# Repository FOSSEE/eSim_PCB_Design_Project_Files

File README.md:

## Task 7 – ESP32-S3 PCB Design Submission

Dear FOSSEE eSim Team,

I am submitting my PCB design as part of the eSim Semester Long Internship – Autumn 2026, Screening Task 7.

### Project Title
ESP32-S3 Development and Interface PCB

### Project Description
The project involves designing a custom PCB integrating an ESP32-S3-WROOM-1 module, 3.3 V voltage regulation, external interfacing connectors and status indication circuitry.

### Submitted Files
- KiCad schematic and PCB project files
- PCB design proposal
- Technical design documentation
- PCB layout and 3D-view images
- Manufacturing files, where applicable

The repository contains the project files and supporting documentation for review.

Thank you for your consideration.

**Submitted by:**  
Siddhant Monde  
Electronics and Telecommunication Engineering  
St. Francis Institute of Technology, Mumbai

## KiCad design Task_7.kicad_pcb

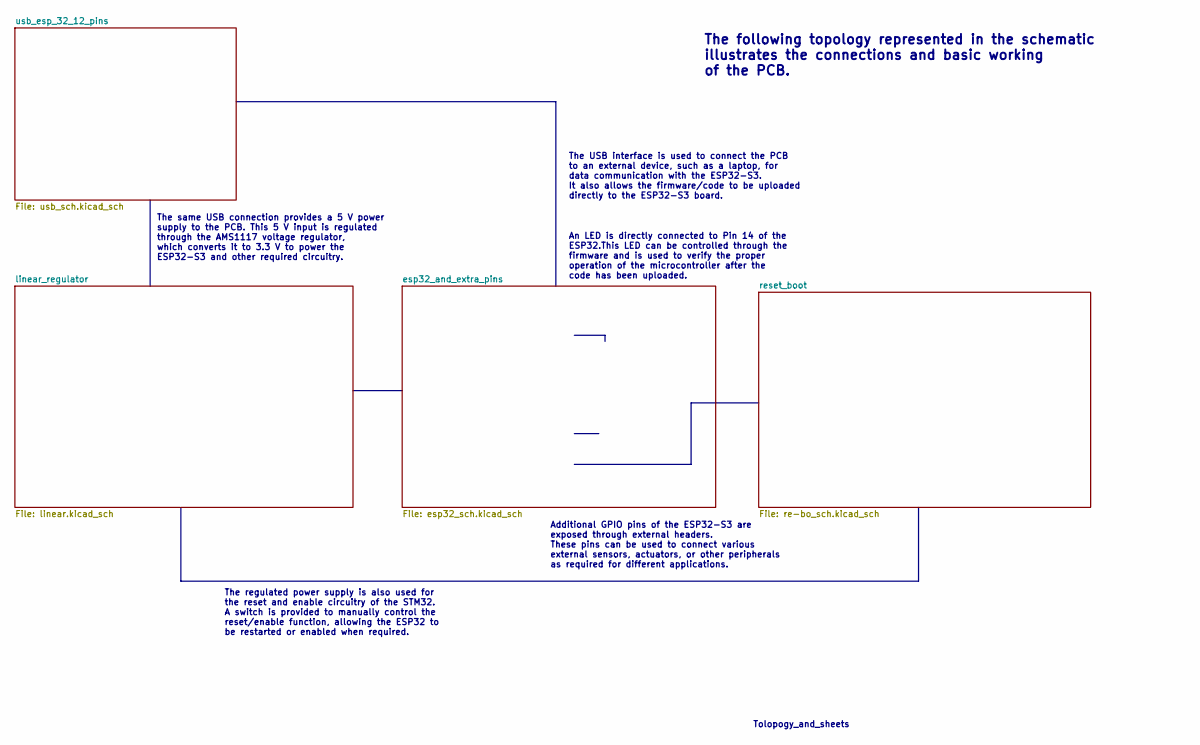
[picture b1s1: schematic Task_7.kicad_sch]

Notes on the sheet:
The following topology represented in the schematic illustrates the connections and basic working of the PCB.
The regulated power supply is also used for the reset and enable circuitry of the STM32. A switch is provided to manually control the reset/enable function, allowing the ESP32 to be restarted or enabled when required.
Additional GPIO pins of the ESP32-S3 are exposed through external headers. These pins can be used to connect various external sensors, actuators, or other peripherals as required for different applications.
The same USB connection provides a 5 V power supply to the PCB. This 5 V input is regulated through the AMS1117 voltage regulator, which converts it to 3.3 V to power the ESP32-S3 and other required circuitry.
The USB interface is used to connect the PCB to an external device, such as a laptop, for data communication with the ESP32-S3. It also allows the firmware/code to be uploaded directly to the ESP32-S3 board.
Tolopogy_and_sheets
An LED is directly connected to Pin 14 of the ESP32.This LED can be controlled through the firmware and is used to verify the proper operation of the microcontroller after the code has been uploaded.

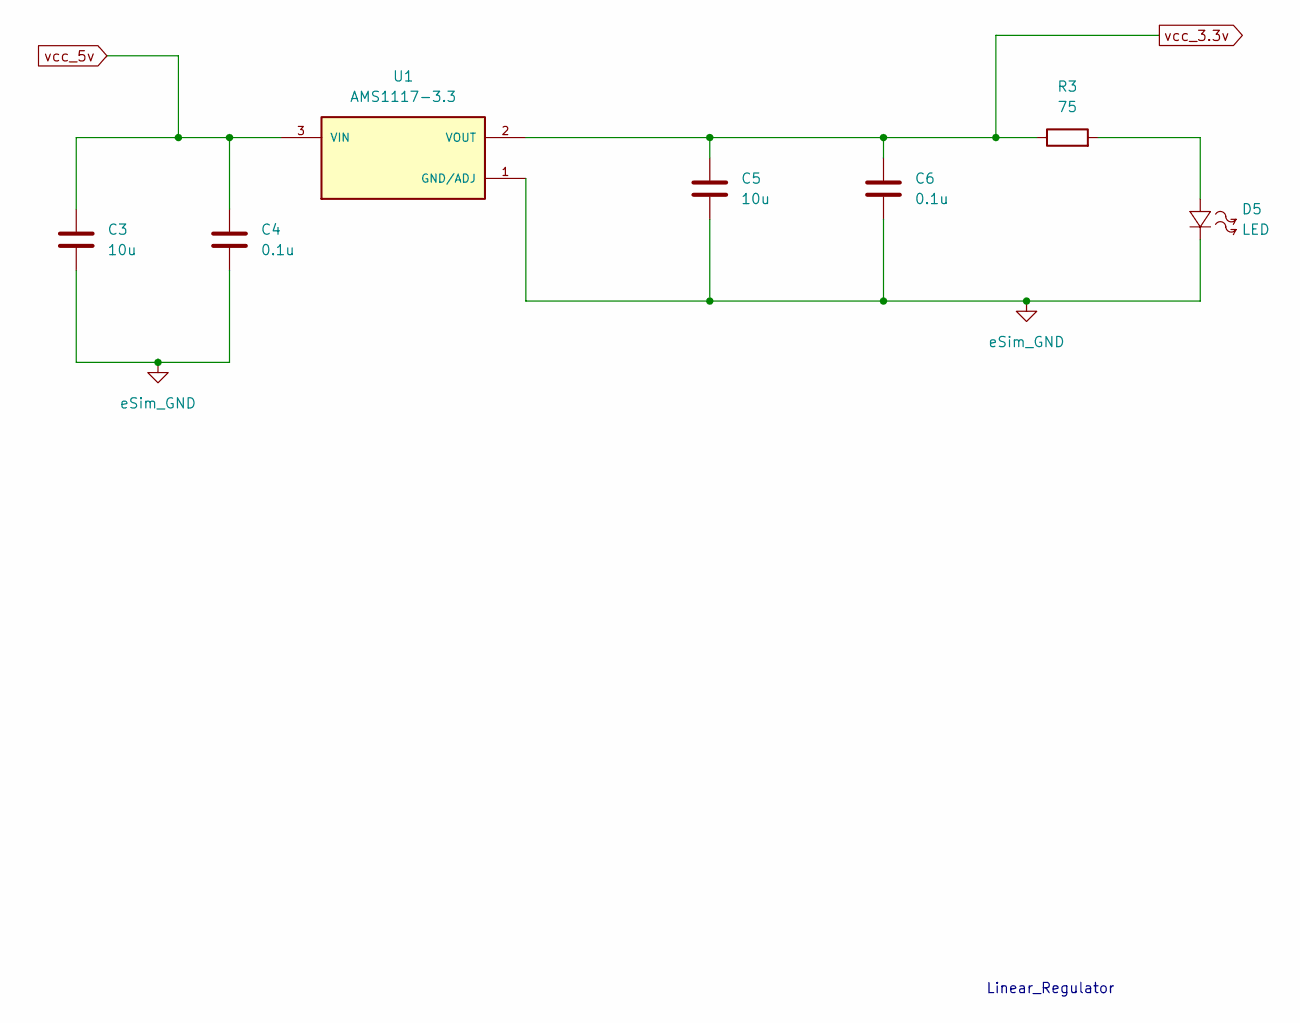
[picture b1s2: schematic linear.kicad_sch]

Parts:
C3, C5: 10u; CP_EIA-1608-08_AVX-J
C4, C6: 0.1u; CP_EIA-1608-08_AVX-J
D5: LED; LED_0805_2012Metric
R3: 75; R_0603_1608Metric
U1: AMS1117-3.3; ams117_footprint; PARTREV N/A

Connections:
GND: C3.1, C4.1, C5.1, C6.1, D5.2 (-), U1.1 (GND/ADJ); also elsewhere on the board
unnamed: D5.1 (+), R3.2
vcc_3.3v: C5.2, C6.2, R3.1, U1.2 (VOUT); also elsewhere on the board
vcc_5v: C3.2, C4.2, U1.3 (VIN); also elsewhere on the board

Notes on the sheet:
Linear_Regulator

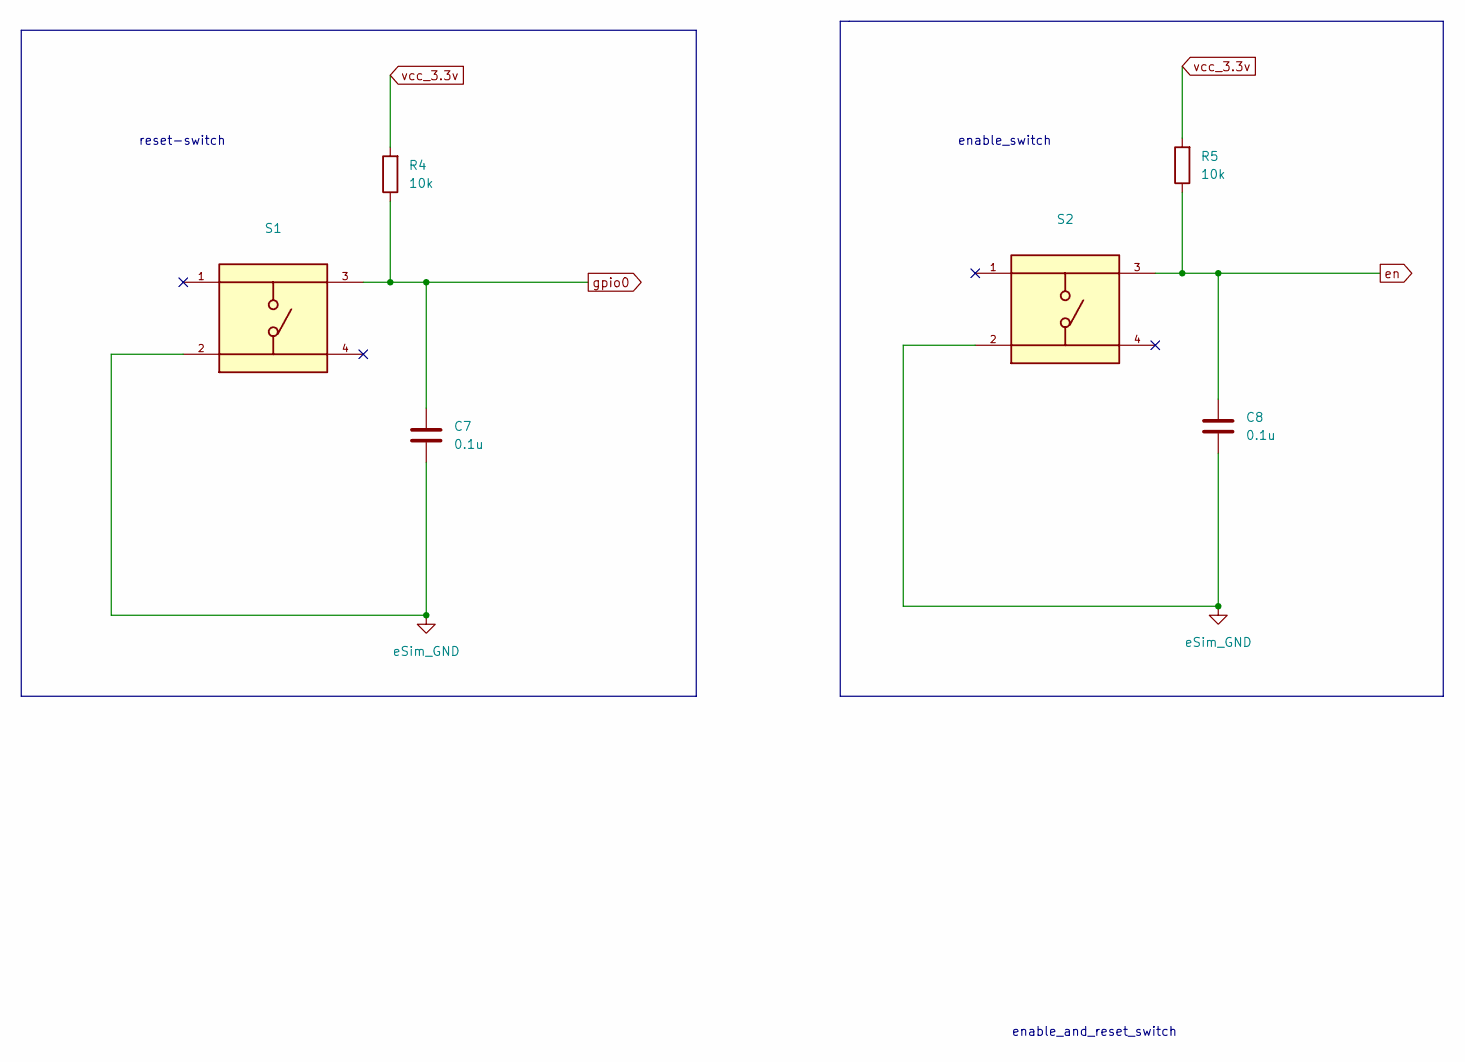
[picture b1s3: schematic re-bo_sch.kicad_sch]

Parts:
C7, C8: 0.1u; CP_EIA-1608-08_AVX-J
R4, R5: 10k; R_0603_1608Metric
S1, S2: TS04-66-55-BK-100-SMT; SW_Push_2P1T_Toggle_CK_PVA1xxH3xxxxxxV2; PARTREV 1.0

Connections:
GND: C7.2, C8.2, S1.2, S2.2; also elsewhere on the board
en: C8.1, R5.1, S2.3; also elsewhere on the board
gpio0: C7.1, R4.1, S1.3; also elsewhere on the board
vcc_3.3v: R4.2, R5.2; also elsewhere on the board

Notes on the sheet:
enable_switch
reset-switch
enable_and_reset_switch

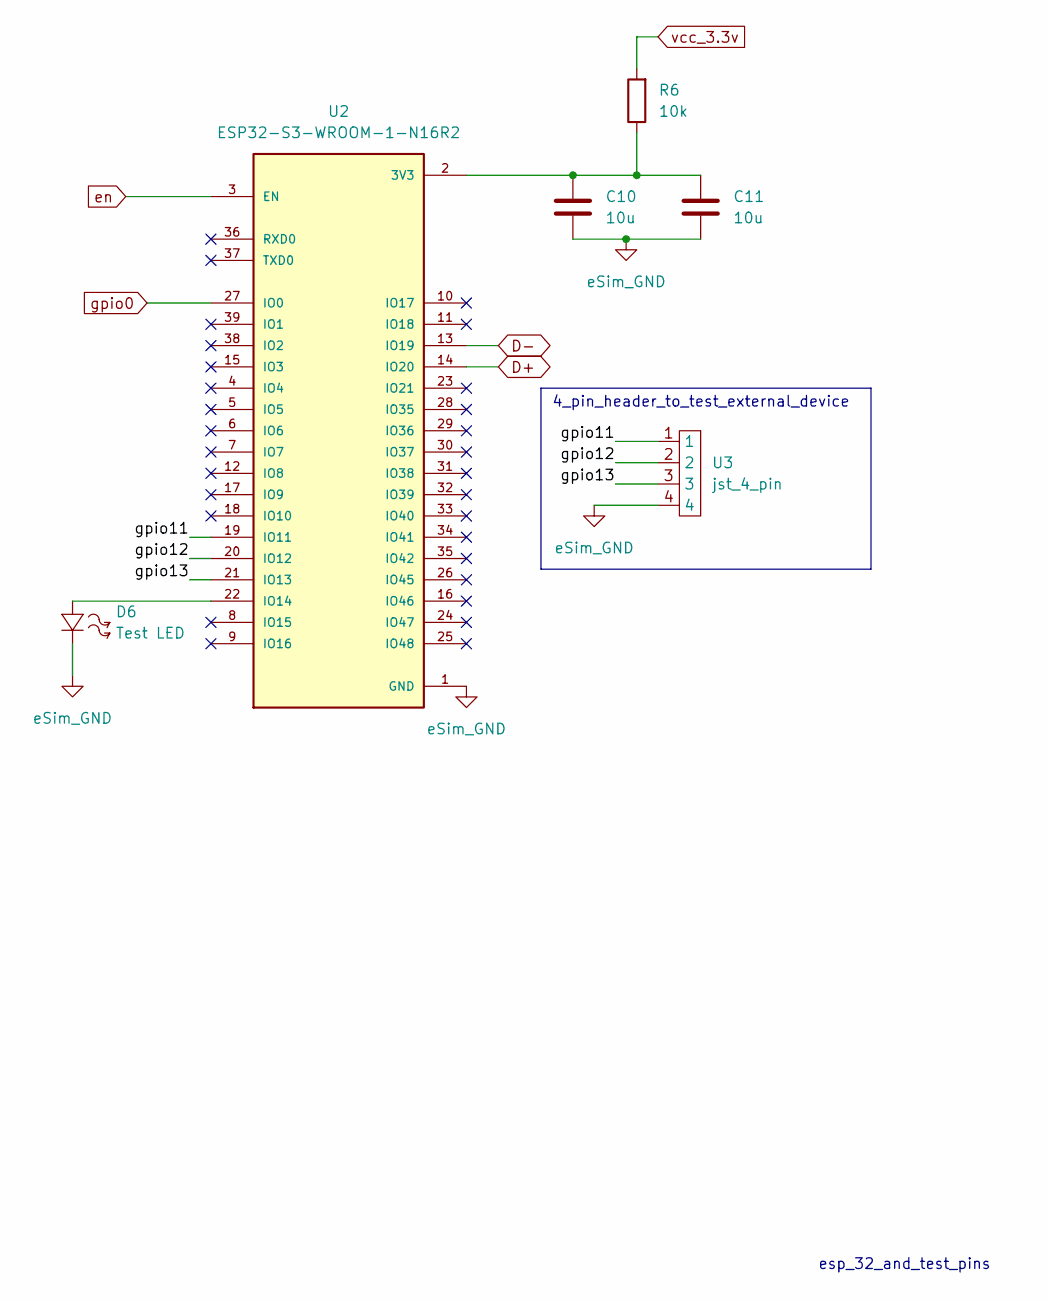
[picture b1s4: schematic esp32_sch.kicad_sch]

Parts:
C10, C11: 10u; CP_EIA-1608-08_AVX-J
D6: Test LED; LED_0805_2012Metric
R6: 10k; R_0603_1608Metric
U2: ESP32-S3-WROOM-1-N16R2; XCVR_ESP32-S3-WROOM-1-N16R2; PARTREV v1.0
U3: jst_4_pin; JST_EH_B4B-EH-A_1x04_P2.50mm_Vertical

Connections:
/esp32_and_extra_pins/gpio11: U2.19 (IO11), U3.1
/esp32_and_extra_pins/gpio12: U2.20 (IO12), U3.2
/esp32_and_extra_pins/gpio13: U2.21 (IO13), U3.3
D+: U2.14 (IO20); also elsewhere on the board
D-: U2.13 (IO19); also elsewhere on the board
GND: C10.2, C11.2, D6.2 (-), U2.1 (GND), U2.40 (GND), U2.41_1 (GND), U2.41_2 (GND), U2.41_3 (GND), U2.41_4 (GND), U2.41_5 (GND), U2.41_6 (GND), U2.41_7 (GND), U2.41_8 (GND), U2.41_9 (GND), U2.41_14, U3.4; also elsewhere on the board
unnamed: C10.1, C11.1, R6.1, U2.2 (3V3)
unnamed: D6.1 (+), U2.22 (IO14)
en: U2.3 (EN); also elsewhere on the board
gpio0: U2.27 (IO0); also elsewhere on the board
vcc_3.3v: R6.2; also elsewhere on the board

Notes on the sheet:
4_pin_header_to_test_external_device
esp_32_and_test_pins

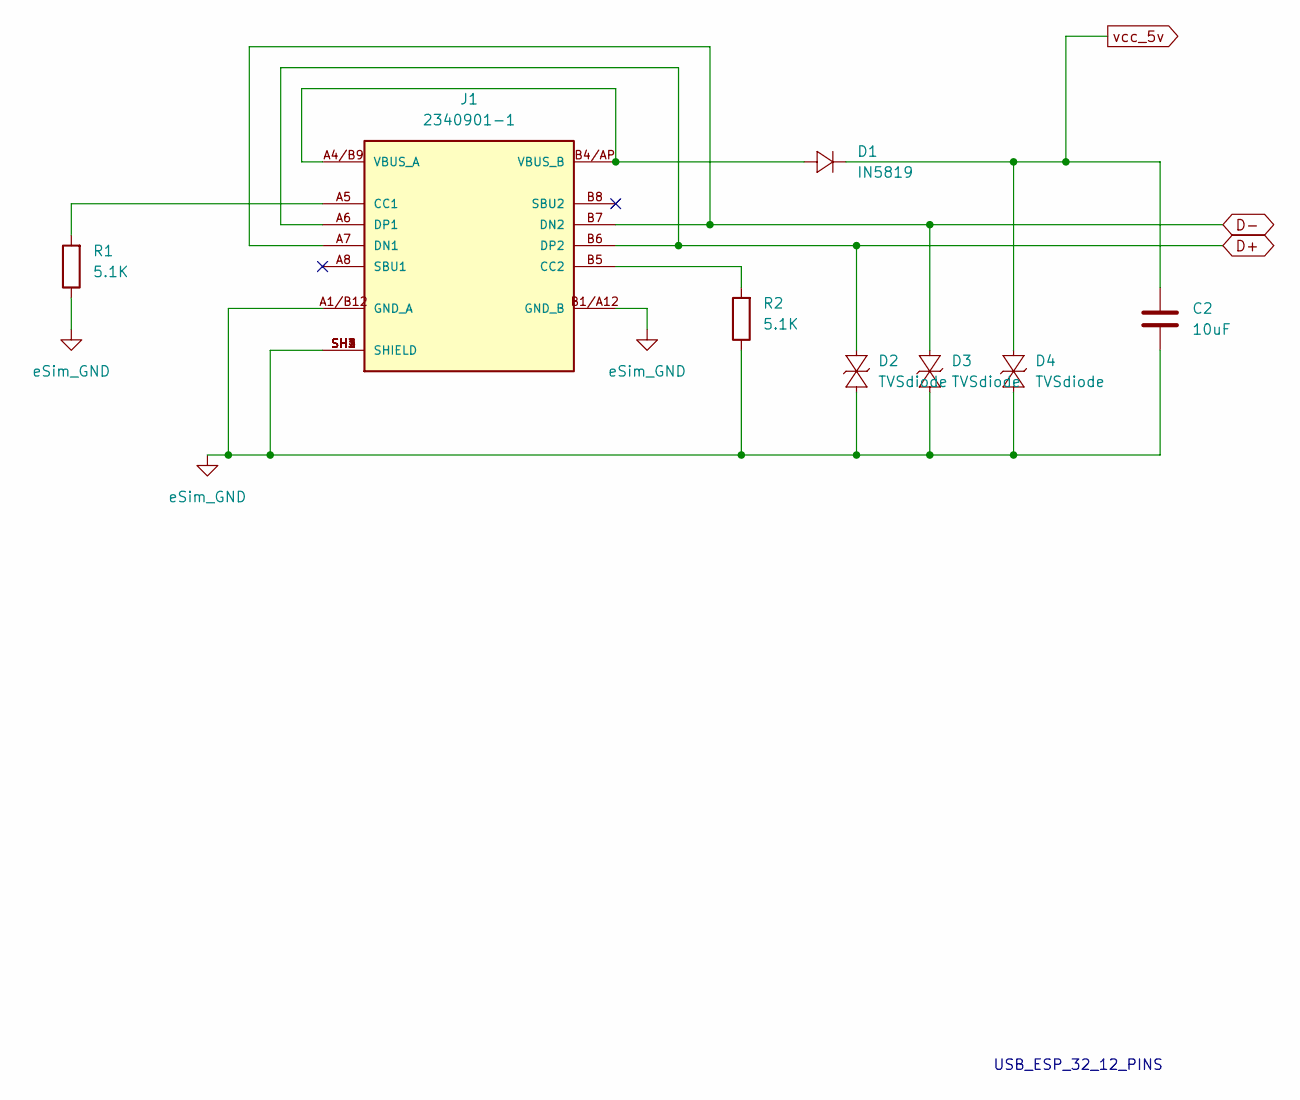
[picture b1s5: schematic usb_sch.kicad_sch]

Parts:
C2: 10uF; CP_EIA-1608-08_AVX-J
D1: IN5819; D_0603_1608Metric
D2, D3, D4: TVSdiode; D_0603_1608Metric
J1: 2340901-1; TE_2340901-1; PARTREV A
R1, R2: 5.1K; R_0603_1608Metric

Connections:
D+: D2.1 (+), J1.A6 (DP1), J1.B6 (DP2); also elsewhere on the board
D-: D3.1 (+), J1.A7 (DN1), J1.B7 (DN2); also elsewhere on the board
GND: C2.2, D2.2 (-), D3.2 (-), D4.2 (-), J1.A1/B12 (GND_A), J1.B1/A12 (GND_B), J1.SH1 (SHIELD), J1.SH2 (SHIELD), J1.SH3 (SHIELD), J1.SH4 (SHIELD), R1.1, R2.1; also elsewhere on the board
unnamed: D1.1 (+), J1.A4/B9 (VBUS_A), J1.B4/AP (VBUS_B)
unnamed: J1.A5 (CC1), R1.2
unnamed: J1.B5 (CC2), R2.2
vcc_5v: C2.1, D1.2 (-), D4.1 (+); also elsewhere on the board

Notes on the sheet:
USB_ESP_32_12_PINS

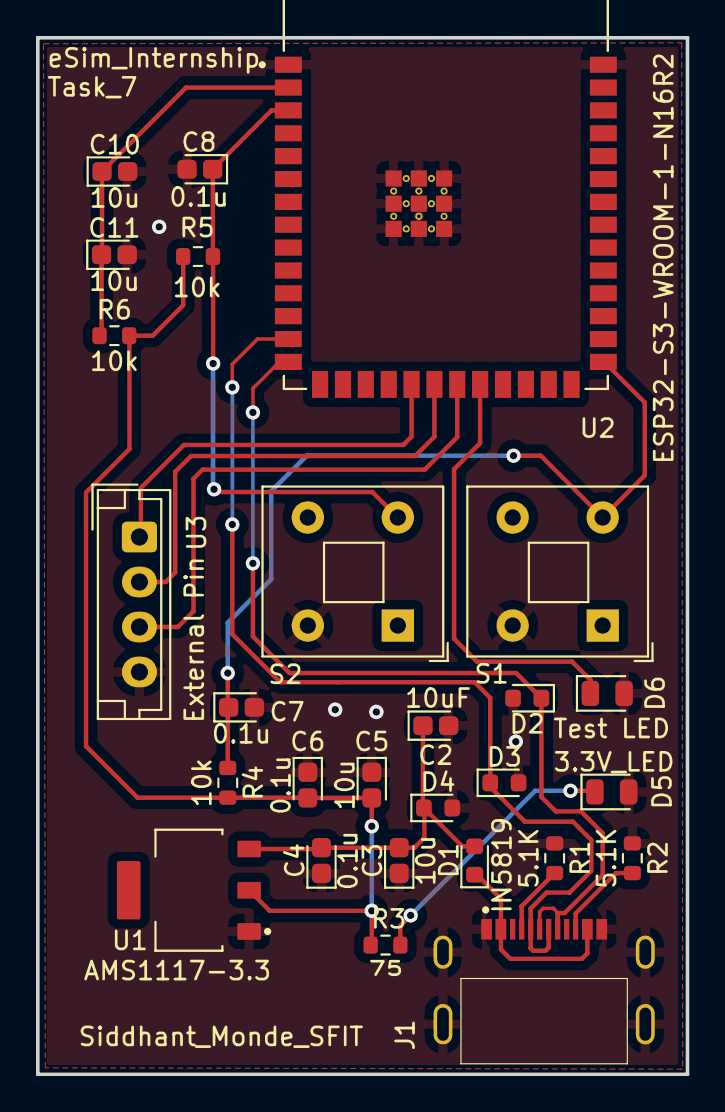
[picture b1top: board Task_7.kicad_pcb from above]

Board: 2 copper layers, 36.1 x 57.6 mm, 27 parts (0 on the bottom side), 16 nets.

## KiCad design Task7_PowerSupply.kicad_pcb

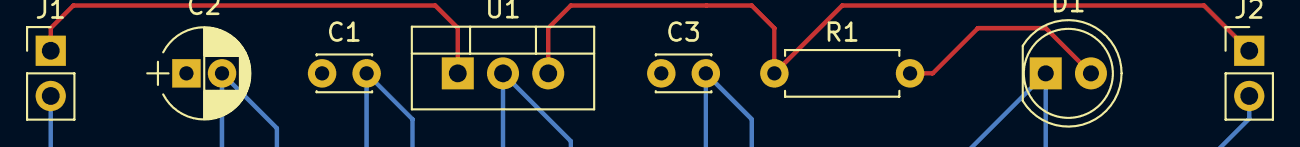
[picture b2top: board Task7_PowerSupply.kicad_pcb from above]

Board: 2 copper layers, 8 parts (0 on the bottom side), 4 nets.

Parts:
C1, C3: eSim_C; C_Disc_D3.0mm_W2.0mm_P2.50mm
C2: eSim_CP1; CP_Radial_D5.0mm_P2.00mm
D1: eSim_LED; LED_D5.0mm
J1, J2: Conn_01x02; Pin_Header_Straight_1x02_Pitch2.54mm
R1: eSim_R; R_Axial_DIN0207_L6.3mm_D2.5mm_P7.62mm_Horizontal
U1: L7805; TO-220_Vertical

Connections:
unnamed: C1.2, C2.2, C3.2, D1.1, J1.2, J2.2, U1.2
unnamed: D1.2, R1.2
unnamed: J1.1, U1.1
unnamed: J2.1, R1.1, U1.3

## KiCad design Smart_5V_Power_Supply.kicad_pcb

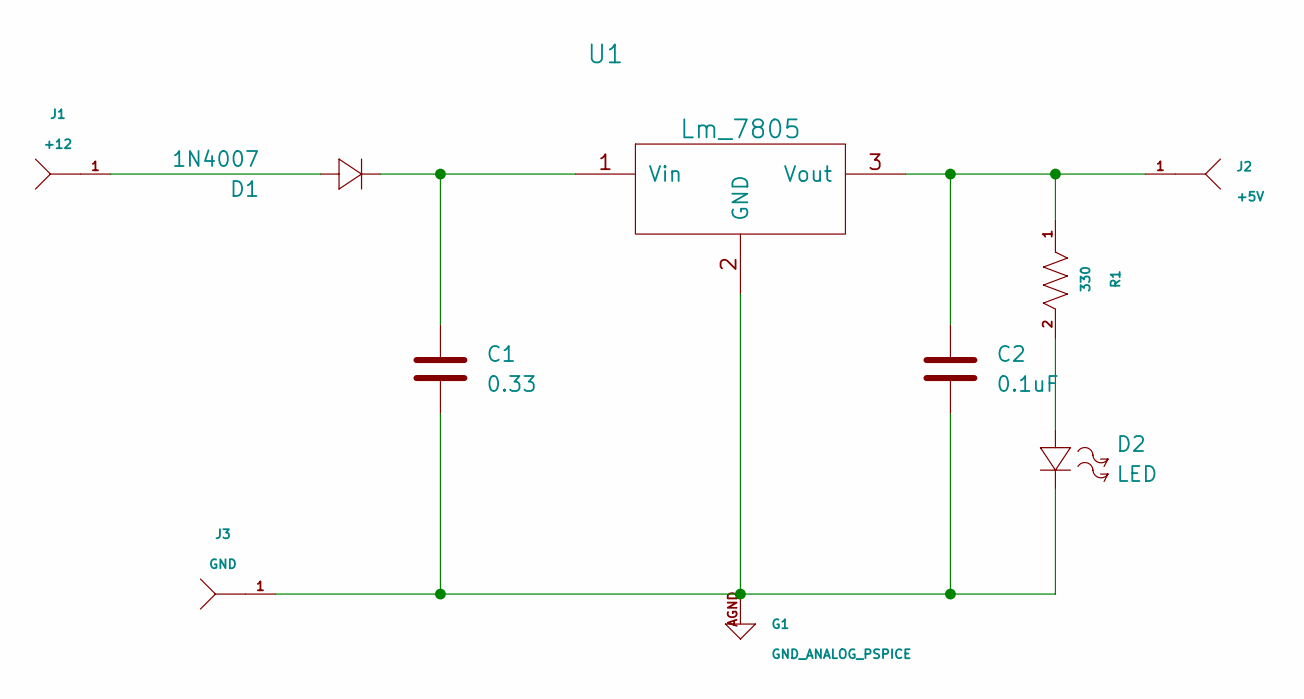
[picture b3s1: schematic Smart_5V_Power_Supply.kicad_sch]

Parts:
C1: 0.33; C_Disc_D5.1mm_W3.2mm_P5.00mm
C2: 0.1uF; C_Disc_D5.1mm_W3.2mm_P5.00mm
D1: 1N4007; D_DO-41_SOD81_P10.16mm_Horizontal
D2: LED; LED_D5.0mm
G1: GND_ANALOG_PSPICE
J1: +12; PinHeader_1x01_P2.54mm_Vertical
J2: +5V; PinHeader_1x01_P2.54mm_Vertical
J3: GND; PinHeader_1x01_P2.54mm_Vertical
R1: 330; R_Axial_DIN0207_L6.3mm_D2.5mm_P10.16mm_Horizontal
U1: Lm_7805; TO-220-3_Vertical

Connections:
unnamed: C1.1, D1.2 (-), U1.1 (Vin)
unnamed: C1.2, C2.2, D2.2 (-), G1.AGND, J3.1, U1.2 (GND)
unnamed: C2.1, J2.1, R1.1, U1.3 (Vout)
unnamed: D1.1 (+), J1.1
unnamed: D2.1 (+), R1.2

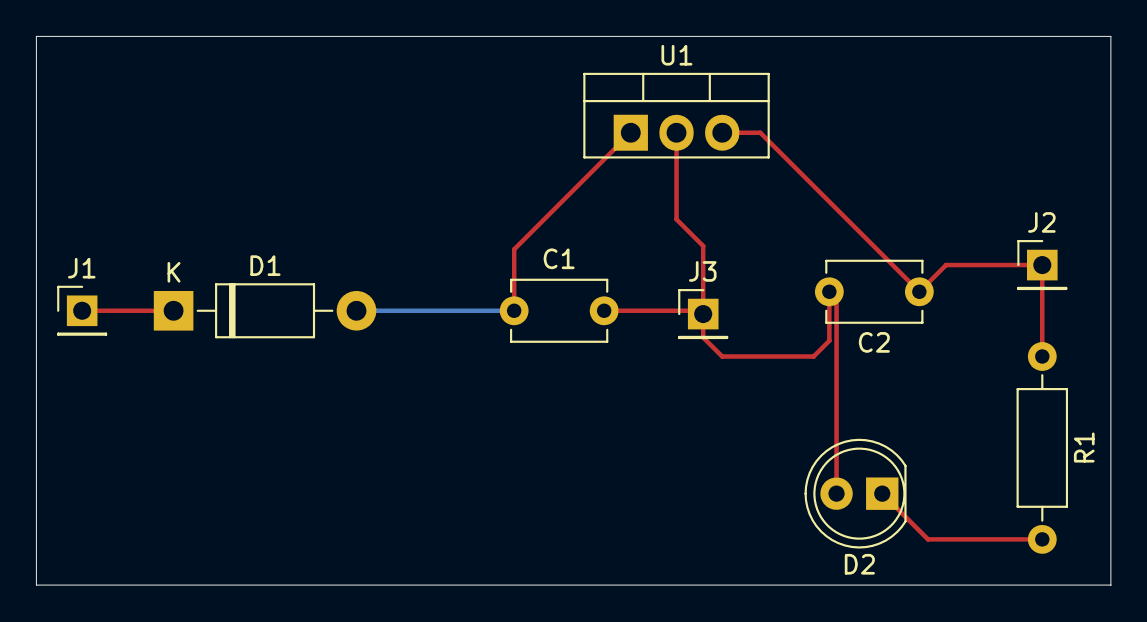
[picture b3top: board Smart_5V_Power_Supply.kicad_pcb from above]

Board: 2 copper layers, 59.7 x 30.5 mm, 9 parts (0 on the bottom side), 5 nets.

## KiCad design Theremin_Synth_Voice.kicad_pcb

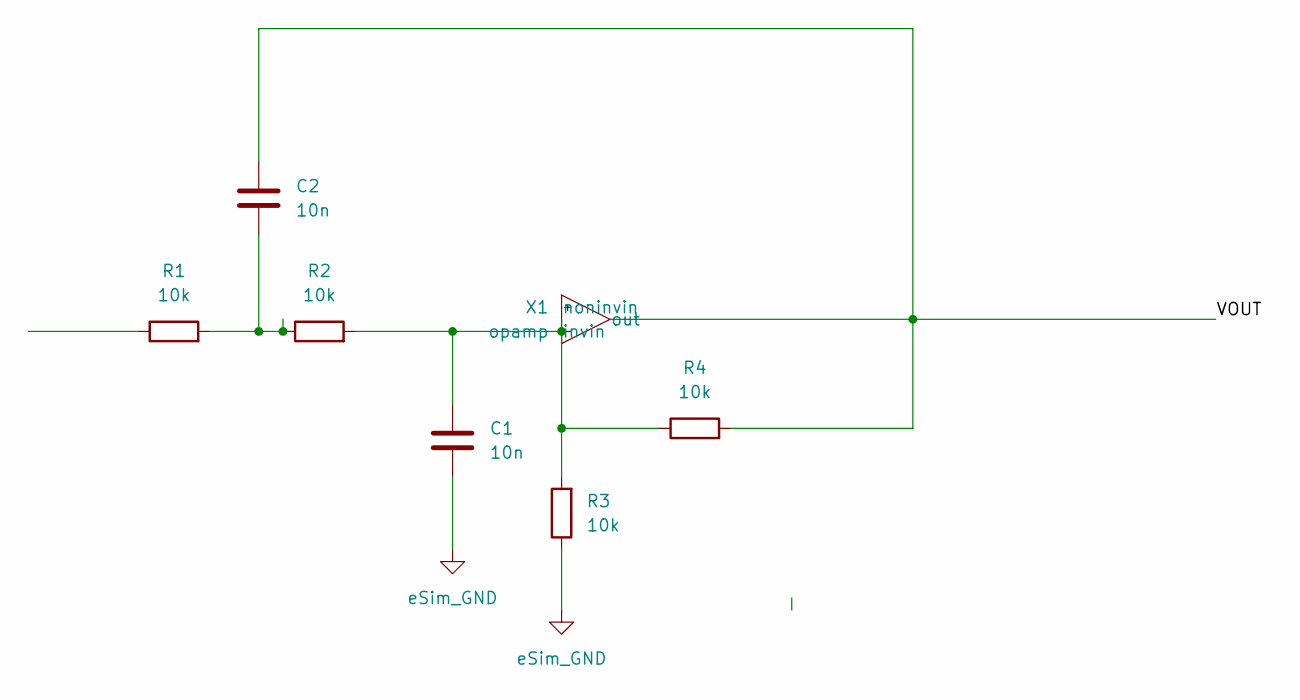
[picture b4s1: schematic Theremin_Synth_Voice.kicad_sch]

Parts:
C1, C2: 10n; CP_Radial_D5.0mm_P2.50mm
R1, R2, R3, R4: 10k; R_Axial_DIN0204_L3.6mm_D1.6mm_P7.62mm_Horizontal
X1: opamp; DIP-8_W7.62mm

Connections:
/VOUT: C2.1, R4.2, X1.3 (out)
GND: C1.1, R3.1
unnamed: C1.2, R2.2, R3.2, R4.1, X1.1 (invin)
unnamed: C2.2, R1.2, R2.1

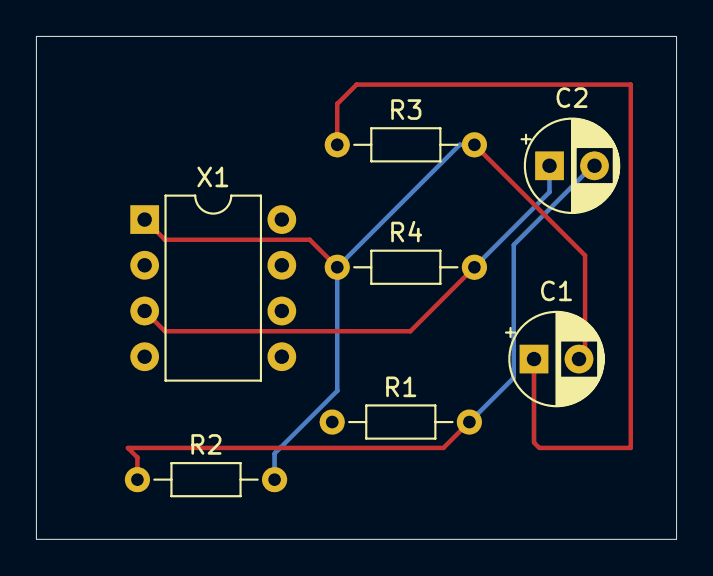
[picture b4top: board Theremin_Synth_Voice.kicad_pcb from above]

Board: 2 copper layers, 35.6 x 27.9 mm, 7 parts (0 on the bottom side), 4 nets.

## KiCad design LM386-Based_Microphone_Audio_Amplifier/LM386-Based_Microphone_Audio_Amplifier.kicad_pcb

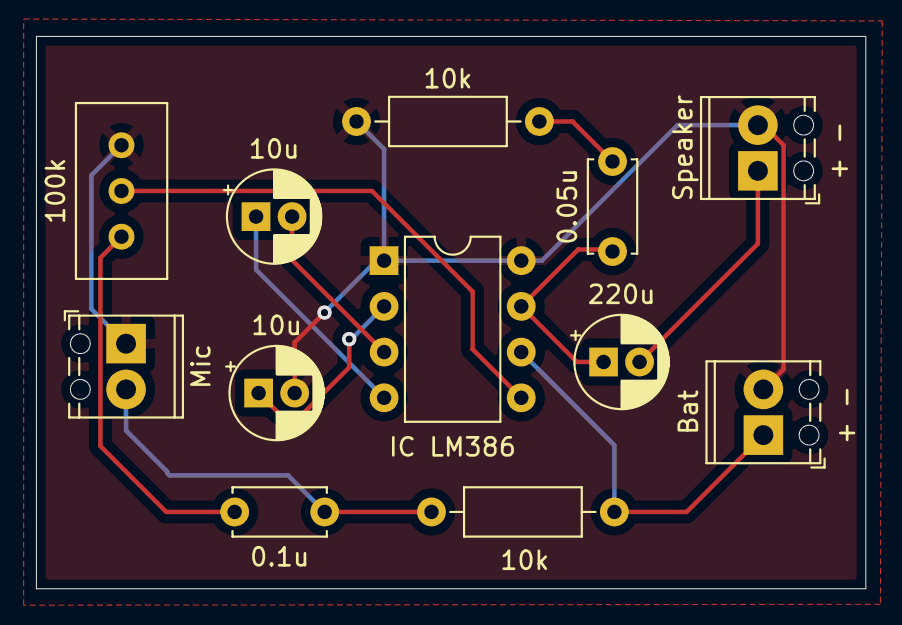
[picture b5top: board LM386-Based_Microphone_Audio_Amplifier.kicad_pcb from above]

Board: 2 copper layers, 46.1 x 30.7 mm, 12 parts (0 on the bottom side), 11 nets.

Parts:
0.1u: 0.1u; C_Disc_D5.0mm_W2.5mm_P5.00mm
0.05u: 0.05u; C_Disc_D5.0mm_W2.5mm_P5.00mm
10k, 10k#2: 10k; R_Axial_DIN0207_L6.3mm_D2.5mm_P10.16mm_Horizontal
10u, 10u#2: 10u; CP_Radial_D5.0mm_P2.00mm
100k: 100k; Potentiometer_Bourns_3296W_Vertical
220u: 220u; CP_Radial_D5.0mm_P2.00mm
Bat: BAT; TerminalBlock_Phoenix_MPT-0,5-2-2.54_1x02_P2.54mm_Horizontal
IC LM386: IC_LM386; DIP-8_W7.62mm
Mic: Mic; TerminalBlock_Phoenix_MPT-0,5-2-2.54_1x02_P2.54mm_Horizontal
Speaker: Speaker; TerminalBlock_Phoenix_MPT-0,5-2-2.54_1x02_P2.54mm_Horizontal

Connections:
GND: 10k#2.1, 10u#2.2, 100k.1, Bat.2, IC LM386.1 (IN-), IC LM386.8 (GND), Mic.1, Speaker.2
unnamed: 0.1u.1, 10k.1, Mic.2
unnamed: 0.1u.2, 100k.3
unnamed: 10u#2.1, IC LM386.2 (BYP)
unnamed: 10u.1, IC LM386.4 (GAIN)
unnamed: 10u.2, IC LM386.3 (GAIN)
unnamed: 0.05u.1, 220u.1, IC LM386.7 (VOUT)
unnamed: 0.05u.2, 10k#2.2
unnamed: 220u.2, Speaker.1
unnamed: 100k.2, IC LM386.5 (IN+)
VCC: 10k.2, Bat.1, IC LM386.6 (VCC)

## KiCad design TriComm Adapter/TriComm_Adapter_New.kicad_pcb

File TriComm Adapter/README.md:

# TriComm Adapter

## Project Overview

The **TriComm Adapter** is a multi-protocol communication interface PCB designed to provide USB connectivity for UART, I²C, and SPI communication through an RJ45 interface. The design integrates multiple dedicated interface controllers with a USB hub to provide a compact and flexible communication adapter for embedded systems and hardware development.

## Features

* USB connectivity through an integrated USB hub.
* USB-to-UART communication using the **CP2102**.
* USB-to-I²C communication using the **CP2112**.
* USB-to-SPI communication using the **CP2130**.
* RJ45 interface for external communication and connectivity.
* On-board 3.3 V power regulation and power selection.
* ESD and power protection provisions.
* Four-layer PCB design with dedicated routing and power/ground planes.
* PCB layout designed and validated using eSim/KiCad.

## Project Files

This directory contains the complete eSim project files, including:

* Schematic files for the main design and hierarchical child sheets.
* PCB layout file.
* eSim project files.
* Netlist and associated project files.
* Supporting files required to open and review the design.

## Validation

The design was subjected to electrical and PCB design validation, including:

* Electrical Rules Check (ERC)
* Design Rules Check (DRC)

The corresponding validation reports are included in the `Documentation` directory.

## Documentation

The project report and ERC/DRC validation reports are provided separately in the `Documentation` directory.

## Tools Used

* **FOSSEE eSim**
* **KiCad**

## Project Type

PCB Design and Hardware Development Project

---

**TriComm Adapter**
Designed as part of the eSim PCB Design Project.

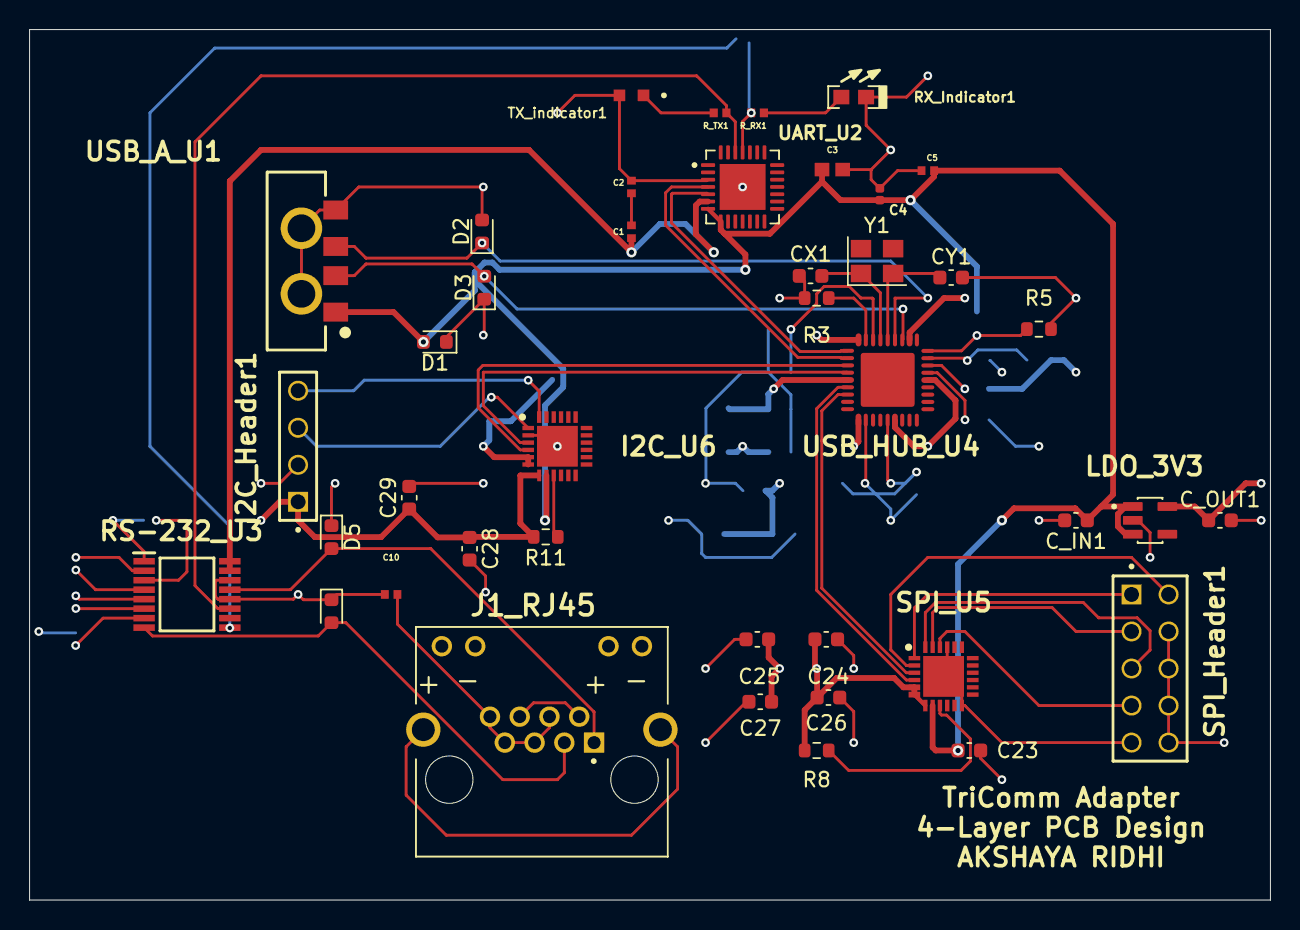
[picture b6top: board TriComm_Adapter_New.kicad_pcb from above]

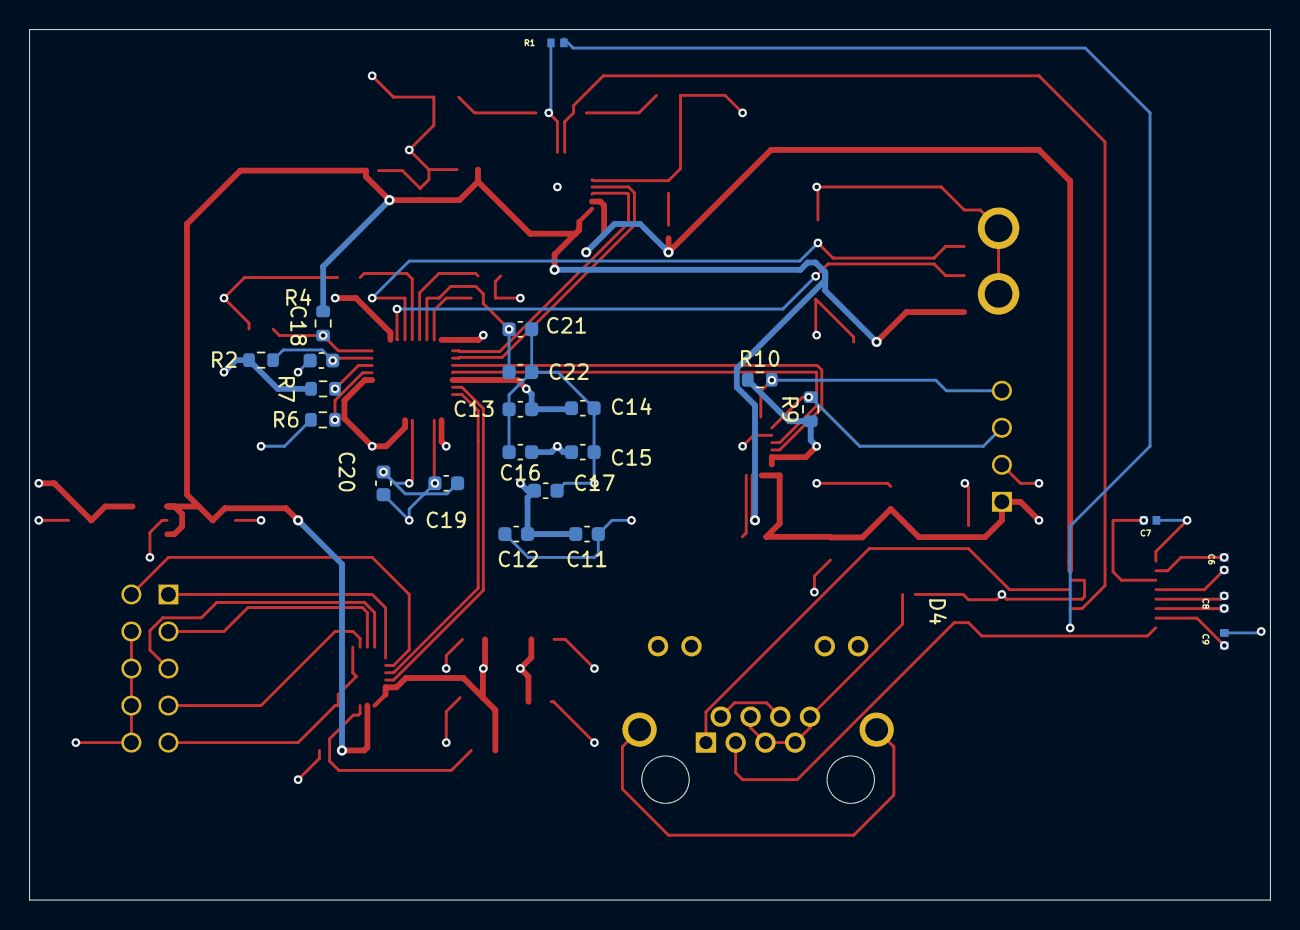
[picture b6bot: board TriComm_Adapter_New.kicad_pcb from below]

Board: 4 copper layers, 85.1 x 59.7 mm, 64 parts (23 on the bottom side), 46 nets.

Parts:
C1: 4.7uF; C1_USB
C2, C5, C6, C7, C8, C9, C10: 100nF; C2_USB
C3: 10uF; CAPC1608X90N
C4: 1uF; CAPC1005X55N
C11, C12, C13, C14, C15, C16, C25, C27, C29: 0.1uF; C_0603_1608Metric
C17: 1.0uF; C_0603_1608Metric
C18, C23, C26: 1uF; C_0603_1608Metric
C19, C21: 10nF; C_0603_1608Metric
C20, C22, C28: 100nF; C_0603_1608Metric
C24: 4.7uF; C_0603_1608Metric
CX1: 18pF; C_0603_1608Metric
CY1: 18pF; C_0603_1608Metric
C_IN1: 1uF; C_0603_1608Metric
C_OUT1: 1uF; C_0603_1608Metric
D1, D2, D3, D4, D5: D_TVS; D_0603_1608Metric
I2C_Header1: TSW-104-07-F-S; SAMTEC_TSW-104-07-F-S
I2C_U6: CP2112-F03-GMR; QFN50P400X400X80-25N-D
J1_RJ45: 2-406549-1; TE_2-406549-1
LDO_3V3: AP2112K-3.3TRG1; SOT95P285X140-5N
R1: 1k; R1_USB
R2, R7: 10K; R_0603_1608Metric
R3: 12K; R_0603_1608Metric
R4, R5, R6: 100K; R_0603_1608Metric
R8, R9, R10, R11: 4.7K; R_0603_1608Metric
RS-232_U3: SN75C3221PWR; SOP65P640X120-16N
RX_Indicator1: APT1608SRCPRV; RX_LED
R_RX1: 330; TX_RX_Resistors
R_TX1: 330; TX_RX_Resistors
SPI_Header1: TSW-105-07-G-D; SAMTEC_TSW-105-07-G-D
SPI_U5: CP2130-F01-GMR; SPI
TX_indicator1: APT1608SGC; TX_LED
UART_U2: CP2102-GM; CP2102
USB_A_U1: 629004113921; USB_A
USB_HUB_U4: USB2513BI-AEZG
Y1: 24 MHz; Crystal_SMD_3225-4Pin_3.2x2.5mm

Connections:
+3.3V: C11.1, C12.1, C13.1, C14.1, C15.1, C16.1, C17.1, C24.1, C25.1, C26.1, C27.1, C28.1, C29.1, C_OUT1.1, I2C_Header1.01, I2C_U6.5 (VIO), I2C_U6.6 (VDD), I2C_U6.7 (REGIN), LDO_3V3.5 (VOUT), R2.1, R7.1, R8.2, R9.1, R10.1, R11.2, SPI_U5.5 (VIO), SPI_U5.6 (VDD), SPI_U5.7 (REGIN), USB_HUB_U4.5 (VDDA33_1), USB_HUB_U4.10 (VDDA33_2), USB_HUB_U4.15 (VDD33_1), USB_HUB_U4.23 (VDD33_2), USB_HUB_U4.29 (VDDA33_3), USB_HUB_U4.36 (VDD33_3)
/I2C_interface/I2C_SCL: I2C_Header1.04, I2C_U6.24 (SCL), R10.2
/I2C_interface/I2C_SDA: I2C_Header1.03, I2C_U6.1 (SDA), R9.2
/USB_Hub_/XTALIN: CX1.1, USB_HUB_U4.33 (CLKIN), Y1.1
/USB_Hub_/XTALOUT: CY1.1, USB_HUB_U4.32 (XTALOUT), Y1.2
/USB_to_UART_via_RJ45/RXD: R1.1, R_RX1.2, UART_U2.25 (RXD)
/USB_to_UART_via_RJ45/TXD: RS-232_U3.11 (DIN), R_TX1.1, UART_U2.26 (TXD)
GND: C2.2, C3.1, C4.1, C5.1, C7.1, C9.1, C10.2, C11.2, C12.2, C13.2, C14.2, C15.2, C16.2, C17.2, C18.2, C19.1, C19.2, C20.1, C20.2, C21.2, C22.1, C23.2, C24.2, C25.2, C26.2, C27.2, C28.2, C29.2, CX1.2, CY1.2, C_IN1.2, C_OUT1.2, D1.1 (A1), D2.2 (A2), D3.1 (A1), D4.1 (A1), D5.1 (A1), I2C_Header1.02, I2C_U6.2 (GND), I2C_U6.25 (EPAD), LDO_3V3.2 (GND), R3.1, R5.1, R6.1, RS-232_U3.1 (~EN), RS-232_U3.12 (FORCEON), RS-232_U3.14 (GND), RX_Indicator1.C, SPI_Header1.04, SPI_Header1.06, SPI_Header1.08, SPI_Header1.10, TX_indicator1.2, UART_U2.3 (GND), UART_U2.29 (GND), USB_A_U1.4 (GND), USB_A_U1.S1, USB_A_U1.S2, USB_HUB_U4.11 (TEST), USB_HUB_U4.14 (CRFILT)
I2C_USB_D+: I2C_U6.3 (D+), USB_HUB_U4.4 (PRT_DIS_P2)
I2C_USB_D-: I2C_U6.4 (D-), USB_HUB_U4.3 (PRT_DIS_M2)
unnamed: C1.2, C2.1
unnamed: C18.1, R2.2, USB_HUB_U4.26 (RESET_N)
unnamed: C21.1, C22.2, USB_HUB_U4.34 (PLLFILT)
unnamed: D5.2 (A2), J1_RJ45.1, RS-232_U3.13 (DOUT)
unnamed: J1_RJ45.2, J1_RJ45.6
unnamed: D4.2 (A2), J1_RJ45.3, RS-232_U3.8 (RIN)
unnamed: C10.1, J1_RJ45.4, J1_RJ45.5, J1_RJ45.7, J1_RJ45.8
unnamed: R3.2, USB_HUB_U4.35 (RBIAS)
unnamed: R4.2, R5.2, USB_HUB_U4.27 (VBUS_DET)
unnamed: R6.2, USB_HUB_U4.24 (CFG_SEL0)
unnamed: R7.2, USB_HUB_U4.25 (CFG_SEL1)
unnamed: R8.1, SPI_U5.9 (~RST)
unnamed: I2C_U6.9 (/RST), R11.1
unnamed: RX_Indicator1.A, R_RX1.1
unnamed: R_TX1.2, TX_indicator1.1
unnamed: SPI_Header1.01, SPI_U5.1 (SCK)
unnamed: SPI_Header1.02, SPI_U5.2 (GND_1)
unnamed: SPI_Header1.09, SPI_U5.12 (GPIO.9_/_~CS9_/_SUSPEND), SPI_U5.21 (GPIO.1_/_~CS1), SPI_U5.25 (GND_2)
unnamed: SPI_Header1.07, SPI_U5.22 (GPIO.0_/_~CS0)
unnamed: SPI_Header1.03, SPI_U5.23 (MOSI)
unnamed: SPI_Header1.05, SPI_U5.24 (MISO)
unnamed: C6.2, RS-232_U3.2 (C1+)
unnamed: C7.2, RS-232_U3.3 (V+)
unnamed: C6.1, RS-232_U3.4 (C1-)
unnamed: C8.2, RS-232_U3.5 (C2+)
unnamed: C8.1, RS-232_U3.6 (C2-)
unnamed: C9.2, RS-232_U3.7 (V-)
unnamed: R1.2, RS-232_U3.9 (ROUT)
SPI_USB_D+: SPI_U5.3 (D+), USB_HUB_U4.7 (PRT_DIS_P3)
SPI_USB_D-: SPI_U5.4 (D-), USB_HUB_U4.6 (PRT_DIS_M3)
UART_USB_D+: UART_U2.4 (D+), USB_HUB_U4.2 (PRT_DIS_P1)
UART_USB_D-: UART_U2.5 (D–), USB_HUB_U4.1 (PRT_DIS_M1)
USB_A_D+: D2.1 (A1), USB_A_U1.3 (D+), USB_HUB_U4.31 (USBDP_UP)
USB_A_D-: D3.2 (A2), USB_A_U1.2 (D-), USB_HUB_U4.30 (USBDM_UP)
VBUS: C3.2, C4.2, C5.2, C23.1, C_IN1.1, D1.2 (A2), I2C_U6.8 (VBUS), LDO_3V3.1 (VIN), LDO_3V3.3 (EN), R4.1, SPI_U5.8 (VBUS), UART_U2.7 (REGIN), UART_U2.8 (VBUS), USB_A_U1.1 (VBUS)
VDD: C1.1, RS-232_U3.15 (VCC), RS-232_U3.16 (~FORCEOFF), UART_U2.6 (VDD)

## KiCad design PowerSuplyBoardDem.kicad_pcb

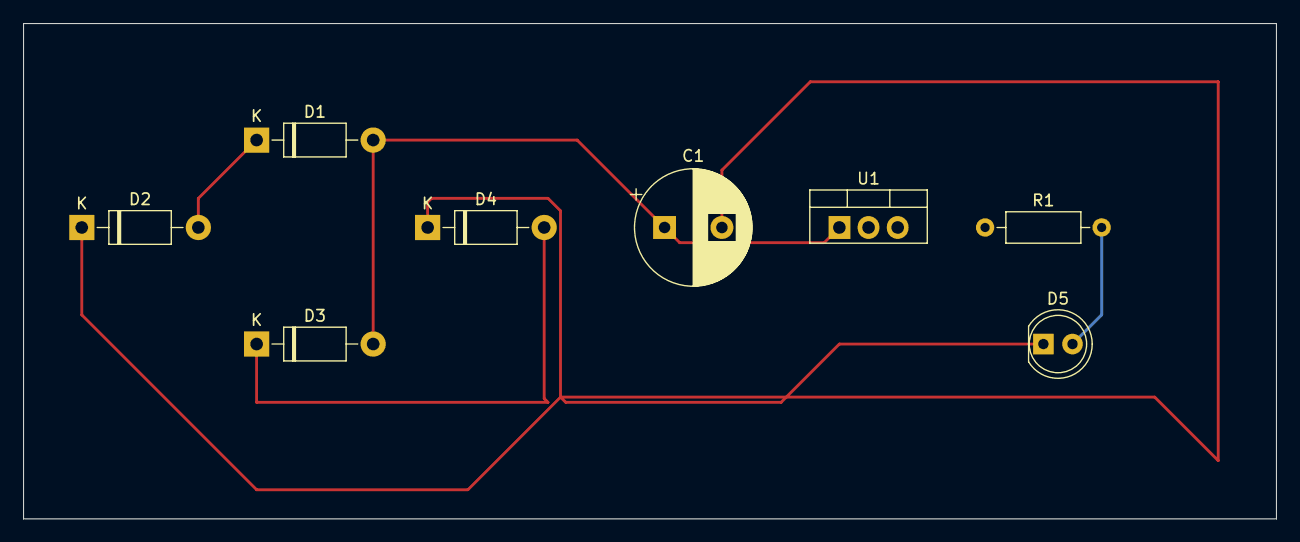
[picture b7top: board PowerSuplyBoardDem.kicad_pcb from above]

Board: 2 copper layers, 109.2 x 43.2 mm, 8 parts (0 on the bottom side), 5 nets.

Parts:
C1: 1000uF; CP_Radial_D10.0mm_P5.00mm
D1, D2, D3, D4: eSim_Diode; D_DO-41_SOD81_P10.16mm_Horizontal
D5: eSim_LED; LED_D5.0mm
R1: 330; R_Axial_DIN0207_L6.3mm_D2.5mm_P10.16mm_Horizontal
U1: LM7805C_PSPICE; TO-220-3_Vertical

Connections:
/GND: C1.2, D2.1 (A), D4.1 (A), D5.1 (A)
/VOUT: C1.1, D1.2 (K), D3.2 (K), U1.1
unnamed: D1.1 (A), D2.2 (K)
unnamed: D3.1 (A), D4.2 (K)
unnamed: D5.2 (K), R1.2

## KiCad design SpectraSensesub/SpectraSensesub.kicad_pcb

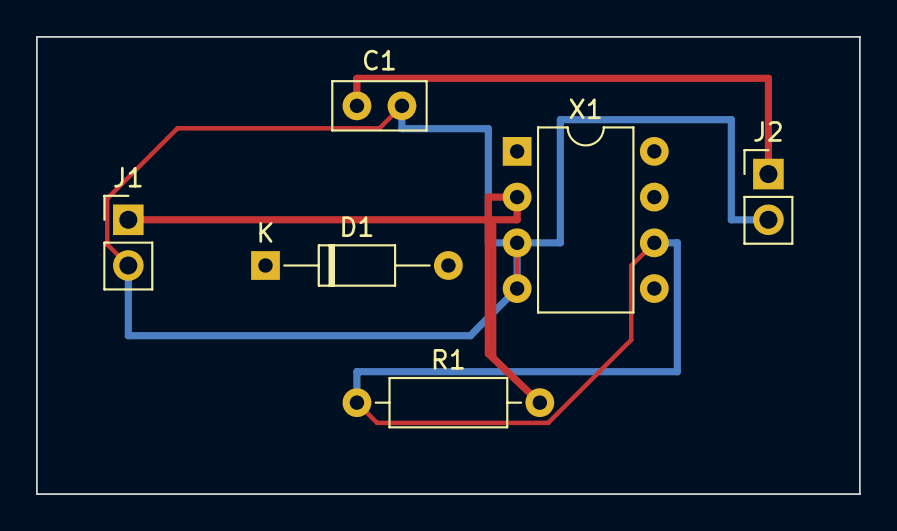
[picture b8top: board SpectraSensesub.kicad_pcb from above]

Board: 2 copper layers, 45.7 x 25.4 mm, 6 parts (0 on the bottom side), 4 nets.

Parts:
C1: 100nF; C_Disc_D5.0mm_W2.5mm_P2.50mm
D1: 1N4148; D_DO-35_SOD27_P10.16mm_Horizontal
J1: SENSOR_IN; PinHeader_1x02_P2.54mm_Vertical
J2: POWER_IN; PinHeader_1x02_P2.54mm_Vertical
R1: 100k; R_Axial_DIN0207_L6.3mm_D2.5mm_P10.16mm_Horizontal
X1: lm_741; DIP-8_W7.62mm

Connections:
GND: C1.2, J1.2, J2.2, X1.3 (non_inv), X1.4 (v_neg)
unnamed: C1.1, J2.1
unnamed: J1.1, R1.2, X1.2 (inv)
unnamed: R1.1, X1.6 (out)
